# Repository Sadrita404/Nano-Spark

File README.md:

<div align="center">
  <table border="0" cellpadding="0" cellspacing="0">
    <tr>
      <td align="center" style="background: #ffffff; border: 1px solid #d0d7de; border-radius: 12px; padding: 16px; box-shadow: 0 4px 12px rgba(0,0,0,0.05);">
        
        <div style="margin-top: 12px; font-family: -apple-system, BlinkMacSystemFont, 'Segoe UI', Helvetica, Arial, sans-serif; font-size: 13px; color: #57606a; font-weight: 500;">
      </td>
    </tr>
  </table>
</div>

| Title | Nano-Spark |
| :-- | :---|
|Author |Sadrita Neogi|

## What's this?
NanoSpark is an Digispark clone with All 6 GPIOs from the attiny available 5V output (direct from USB) 3V3 output (via AMS1117 voltage regulator) Power LED Onboard LED connected to PB1 USB-A connector

## Why I built it ?

To learn more about electronics and PCB design and also because the Digispark boards don't have a 3V3 output. This board also uses USB-A instead of Micro USB so I don't need any extra cable to connect to my laptop.

## Programming

The attiny chip needs to be flashed with a bootloader so that you can use it without a programmer (like an Arduino board). 
#### [Bootloader](https://github.com/Sadrita404/Nano-Spark/tree/main/Boot%20loader)

**[GUIDE](https://circuitdigest.com/microcontroller-projects/attiny85-ic-programming-through-usb-using-digispark-bootloader)**

These tutorials use the micronucleus bootloader used by the Digispark attiny boards.

There is an onboard LED hardwired to PB1 so you can get your blink sketch running without any extra hardware.

## Features

* All 6 GPIOs from the attiny available 

* 5V output (direct from USB)

* 3V3 output (via AMS1117 voltage regulator)

* Power LED

* Onboard LED connected to PB1

* USB-A connector

<div align="center">

| | PCB Designing | |
| :---: | :---: | :---: |
|  |  |  |
|  |  |  |

<div align="center">
  <h2> Final Look </h2>
  <table border="0" cellpadding="10" cellspacing="0" style="border-collapse: collapse;">
    <tr>
      <!-- FRONT SIDE CARD -->
      <td align="center" valign="top" width="50%" style="background: #ffffff; border: 1px solid #d0d7de; border-radius: 12px; padding: 16px; box-shadow: 0 4px 12px rgba(0,0,0,0.05);">
        
        <div style="margin-top: 12px; font-family: -apple-system, BlinkMacSystemFont, 'Segoe UI', Helvetica, Arial, sans-serif; font-size: 13px; color: #57606a; font-weight: 600; text-transform: uppercase; letter-spacing: 0.5px;">
          ▲ Front Side View
        </div>
      </td>
      <!-- SPACER FOR GITHUB MOBILE DEGRADATION -->
      <td width="2%">&nbsp;</td>
      <!-- BACK SIDE CARD -->
      <td align="center" valign="top" width="50%" style="background: #ffffff; border: 1px solid #d0d7de; border-radius: 12px; padding: 16px; box-shadow: 0 4px 12px rgba(0,0,0,0.05);">
        
        <div style="margin-top: 12px; font-family: -apple-system, BlinkMacSystemFont, 'Segoe UI', Helvetica, Arial, sans-serif; font-size: 13px; color: #57606a; font-weight: 600; text-transform: uppercase; letter-spacing: 0.5px;">
          ▲ Back Side View
        </div>
      </td>
    </tr>
  </table>
</div>
</div>

<div align="center">
  <h2> Bill of Materials </h2>
</div>

| Name | Purpose | Qty | Total (USD) | Link | Distributor |
| :--- | :--- | :---: | :---: | :---: | :--- |
| PCB Board | The main Board | 5 | 2.10 | [jlcpcb](https://jlcpcb.com) | jlcpcb |
| USB-A male connector (MOLEX 48037-0001) | For the connector | 10 | 0.95 | [flyrobo](https://www.flyrobo.in/usb-type-4-pin-male-connector-socket?tracking=ads&srsltid=AfmBOophN-P9nD74dwqi0C-oFKkGJusqnoVQ49TIJ7Mypo4yTeV0mhCgyZ8) | flyrobo |
| Pin Headers (2x5) | For the connector | 5 | 0.24 | [robu](https://robu.in/product/1-month-warranty-921/) | robu |
| ATTINY13A-PU-MICROCHIP | The main chip | 3 | 5.71 | [robu](https://robu.in/product/attiny13a-pu-microchip-8-bit-mcu-low-power-high-performance-avr-attiny-family-attiny13-series-microcontrollers-avr/) | robu |
| 8 Pin DIP IC Socket Base Adaptor | For the chip | 5 | 0.26 | [robu](https://robu.in/product/8-pin-dip-ic-socket-base-adaptor-pack-of-10/) | robu |
| AMS1117 SMD voltage regulator | For Power control | 10 | 0.85 | [robu](https://robu.in/product/ams1117-3-3v-1a-sot-223-voltage-regulator-ic-pack-of-5-ics/?gad_source=1&gad_campaignid=17427802703&gbraid=0AAAAADvLFWeFunRL4eOrQvteNCIPCpvtP&gclid=Cj0KCQjwr4jSBhCSARIsAOX1E-LzS-G1lXeBRDXJ5HAJ51iWCYA7cqD56WnAvNN4MPlpvitz_v-2KbQaAvZoEALw_wcB) | robu |
| 1k Ohm 0.5W (moq 10) | resistor (for USB) | 10 | 0.11 | [robu](https://robu.in/product/1k-ohm-0-5w-metal-film-resistor-pack-of-50/) | robu |
| 68Ω (moq 10) | resistor (for USB) | 10 | 0.12 | [robu](https://robu.in/product/68-ohm-1w-metal-film-resistor-pack-of-40/) | robu |
| SMD 1206 LED (moq 10 ) | The main led | 10 | 0.20 | [robu](https://robu.in/product/1206-surface-mount-led-orange-50-pcs/) | robu |
| 470Ω (moq 10) | For the leds | 10 | 0.11 | [robu](https://robu.in/product/470-ohm-0-25w-metal-film-resistor-pack-of-100/?gad_source=1&gad_campaignid=17427802703&gbraid=0AAAAADvLFWeFunRL4eOrQvteNCIPCpvtP&gclid=Cj0KCQjwr4jSBhCSARIsAOX1E-IUyQc4-tC1BtG_hmUfrMOzM83BJ4yaenllbA7nt-rOSE-xktnRRhgaApbSEALw_wcB) | robu |

<div align="center">
  <table border="0" cellpadding="0" cellspacing="0" style="border-collapse: collapse; max-width: 600px;">
    <tr>
      <td style="background: #ffffff; border: 1px solid #d0d7de; border-radius: 12px; padding: 20px; box-shadow: 0 4px 12px rgba(0,0,0,0.05); font-family: -apple-system, BlinkMacSystemFont, 'Segoe UI', Helvetica, Arial, sans-serif;">
        <div style="font-size: 16px; font-weight: 600; color: #24292f; margin-bottom: 12px; border-bottom: 1px solid #d0d7de; padding-bottom: 8px;">
           Final Summary Title
        </div>
        <table width="100%" border="0" style="border-collapse: collapse; font-size: 14px; color: #57606a;">
          <tr>
            <td style="padding: 4px 0;">Component Subtotal:</td>
            <td align="right" style="font-weight: 500; color: #24292f;">$10.65</td>
          </tr>
          <tr>
            <td style="padding: 4px 0;">Shipping Cost(incl. PCB):</td>
            <td align="right" style="font-weight: 500; color: #24292f;">$10.92</td>
          </tr>
          <tr>
            <td style="padding: 4px 0; padding-bottom: 8px;">Tax:</td>
            <td align="right" style="font-weight: 500; color: #24292f;">$1.5</td>
          </tr>
          <tr style="border-top: 1px dashed #d0d7de;">
            <td style="padding: 12px 0 0 0; font-weight: 600; color: #24292f; font-size: 15px;">Net Total Cost:</td>
            <td align="right" style="padding: 12px 0 0 0; font-weight: bold; color: #2da44e; font-size: 18px;">$23.07</td>
          </tr>
          <tr>
            <td style="padding: 2px 0 0 0; font-size: 11px; color: #8c959f;">Projected Budget Allocation:</td>
            <td align="right" style="padding: 2px 0 0 0; font-weight: 500; font-size: 12px; color: #8c959f;">$24</td>
          </tr>
        </table>
      </td>
    </tr>
  </table>
</div>

---
#### Please approve this project I have give my best in make the pcb design 

**Project Under Hack Club**

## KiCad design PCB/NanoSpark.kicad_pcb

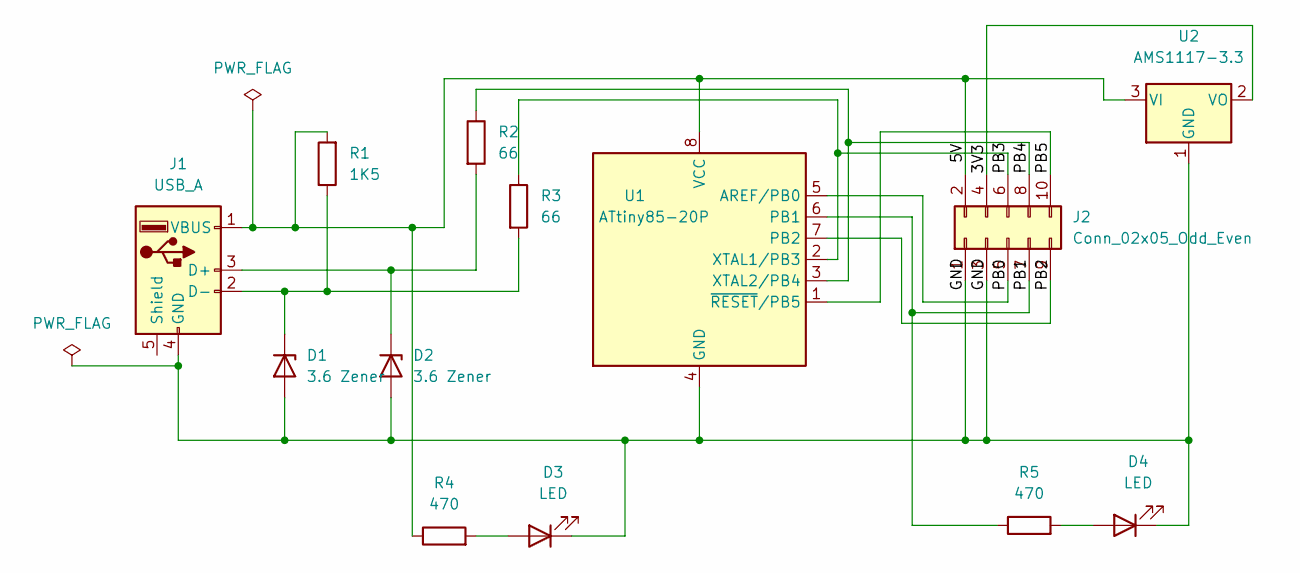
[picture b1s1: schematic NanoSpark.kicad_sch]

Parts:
D1, D2: 3.6 Zener; D_DO-34_SOD68_P7.62mm_Horizontal
D3, D4: LED; LED_1206_3216Metric_Pad1.42x1.75mm_HandSolder
J1: USB_A; MOLEX_48037-0001
J2: Conn_02x05_Odd_Even; PinSocket_2x05_P2.54mm_Vertical
R1: 1K5; R_Axial_DIN0207_L6.3mm_D2.5mm_P7.62mm_Horizontal
R2, R3: 66; R_Axial_DIN0207_L6.3mm_D2.5mm_P7.62mm_Horizontal
R4, R5: 470; R_Axial_DIN0207_L6.3mm_D2.5mm_P7.62mm_Horizontal
U1: ATtiny85-20P; DIP-8_W7.62mm_Socket
U2: AMS1117-3.3; SOT-223-3_TabPin2

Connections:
/3V3: J2.4, U2.2 (VO)
/5V: J1.1 (VBUS), J2.2, R1.2, R4.1, U1.8 (VCC), U2.3 (VI)
/GND: D1.2 (A), D2.2 (A), D3.1 (K), D4.1 (K), J1.4 (GND), J2.1, J2.3, U1.4 (GND), U2.1 (GND)
/PB0: J2.5, U1.5 (AREF/PB0)
/PB1: J2.7, R5.1, U1.6 (PB1)
/PB2: J2.9, U1.7 (PB2)
/PB3: J2.6, R3.1, U1.2 (XTAL1/PB3)
/PB4: J2.8, R2.1, U1.3 (XTAL2/PB4)
/PB5: J2.10, U1.1 (~RESET/PB5)
unnamed: D1.1 (K), J1.2 (D-), R1.1, R3.2
unnamed: D2.1 (K), J1.3 (D+), R2.2
unnamed: D3.2 (A), R4.2
unnamed: D4.2 (A), R5.2

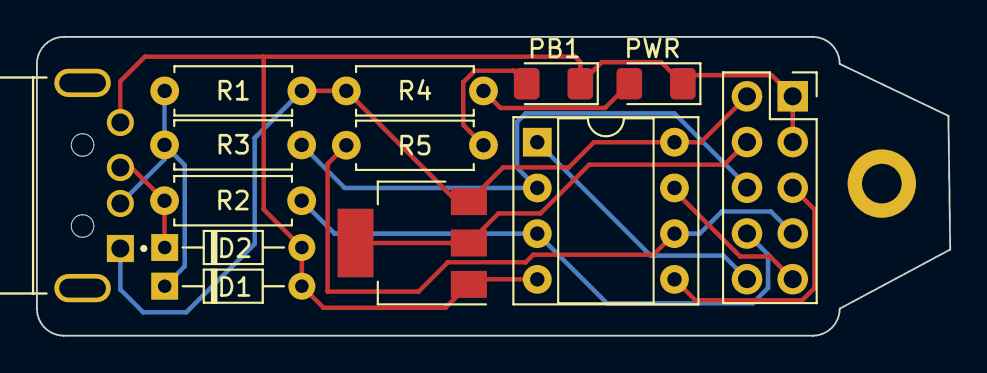
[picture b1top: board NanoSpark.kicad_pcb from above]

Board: 2 copper layers, 50.7 x 16.6 mm, 13 parts (0 on the bottom side), 13 nets.

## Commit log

2026-06-29 gerber added
2026-06-29 BOM added
2026-06-29 project screenshot added
